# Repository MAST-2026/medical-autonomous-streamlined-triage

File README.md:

# MAST Hackathon Project
Shane Abbott, Justin Amaya, Tyler Marleton, Christian White, Karla "Kenny" Madrigal

## Overview
### Key Design Criteria
Continuous vitals monitoring from wearable patient devices.

Automatic triage status information when patient conditions change.

Real-time transmission of patient data to hospitals.

Reduced workload for EMS personnel, allowing responders to focus on treatment instead of communications.

## Components (Tentative)

### 1. Patient Monitoring Device
Strapped onto the patient as a harness, monitoring vitals such as heart rate, blood pressure, temperature, etc. The deivce would transmit information to the ARU in the vehicle automatically, no human input is necessary.

### 2. Ambulance Repeater Unit
Amplifies transmissions from the patient monitoring device to nearby hospitals. High wattage to counter urban RF environments. Pings the HTU for open beds and/or other qualifying information and services. Receives PMD data.

### 3. Hospital Transciever Unit
Located in the hospital, possibly near the radio equipment. Should have excellent RX capabilities. The final step in the process, this is what the hospital staff see, the end product of all incoming patients, in one place.

_Kenny: Question, could a filtering system allow doctors to subscribe to patient updates in real-time, receiving only information relevant to their assigned cases? Also, how do cases get assigned? I doubt whether any of these questions are within the scope of our project, and I think we're better off focusing on the existing components._

## Project Structure
I'd like for each project inside each directory (electrical/firmware/assembly) to have its own `DECISIONS.md` so we can keep track of... decisions.

I've initialized KiCad and PlatformIO projects in the electrical/firmware directories. Mech team (Christian, Justin, Shane) can decide how they want to structure the assembly directory.

```
├── patient-monitoring-device/
│   ├── electrical
│   ├── firmware
│   ├── assembly
│   └── DECISIONS.md
├── ambulance-repeater/
│   ├── electrical
│   ├── firmware
│   ├── assembly
│   └── DECISIONS.md
├── hospital-transciever/
│   ├── electrical
│   ├── firmware
│   ├── assembly
│   └── DECISIONS.md
│   
└── README.md
```

## Getting Started

### Prerequisites
- PlatformIO is an extension for VSCode. Feel free to check out [this video on YouTube](https://www.youtube.com/watch?v=PYSy_PLjytQ)

## Contributing

1. CLONE the repository, not fork. i mean either way doesnt matter but for the sake of simplicit. yas.
2. Create a feature branch (`git checkout -b feature/your-feature`)
3. Commit changes (`git commit -m 'Add feature'`)
4. Push to branch (`git push origin feature/your-feature`)
5. Open a Pull Request. PRs are to merge from your `feature/` branches to the `main` branch

## TODO

- [ ] Define clear project outcome and success criteria
- [ ] [Add additional tasks]

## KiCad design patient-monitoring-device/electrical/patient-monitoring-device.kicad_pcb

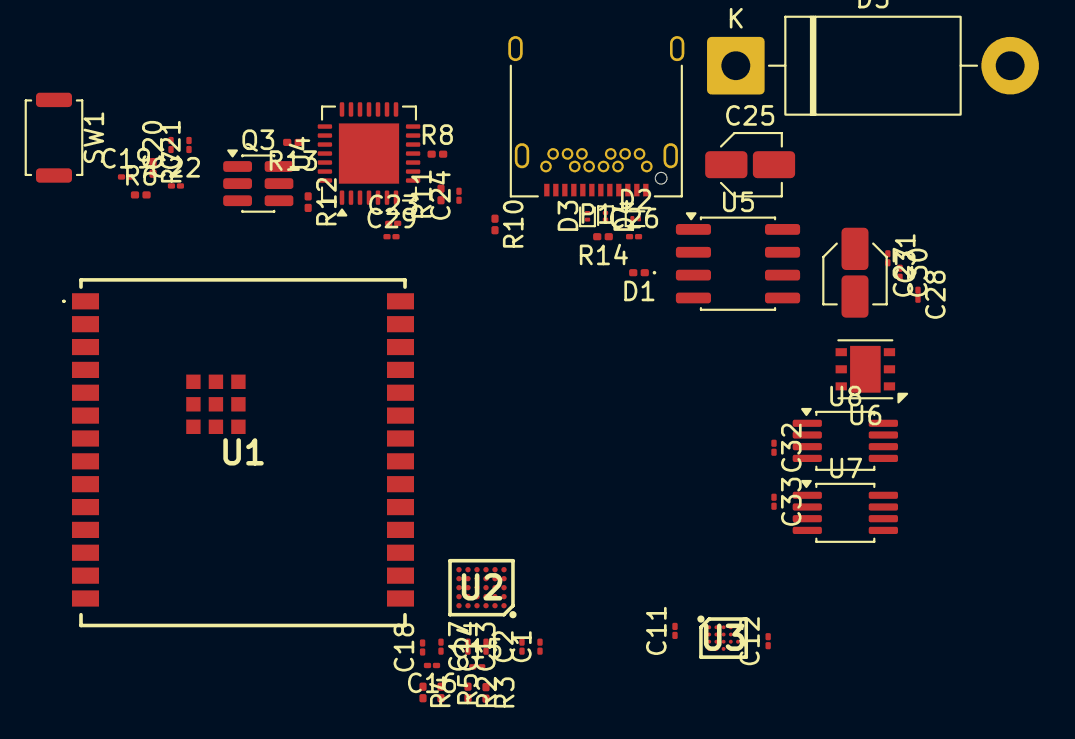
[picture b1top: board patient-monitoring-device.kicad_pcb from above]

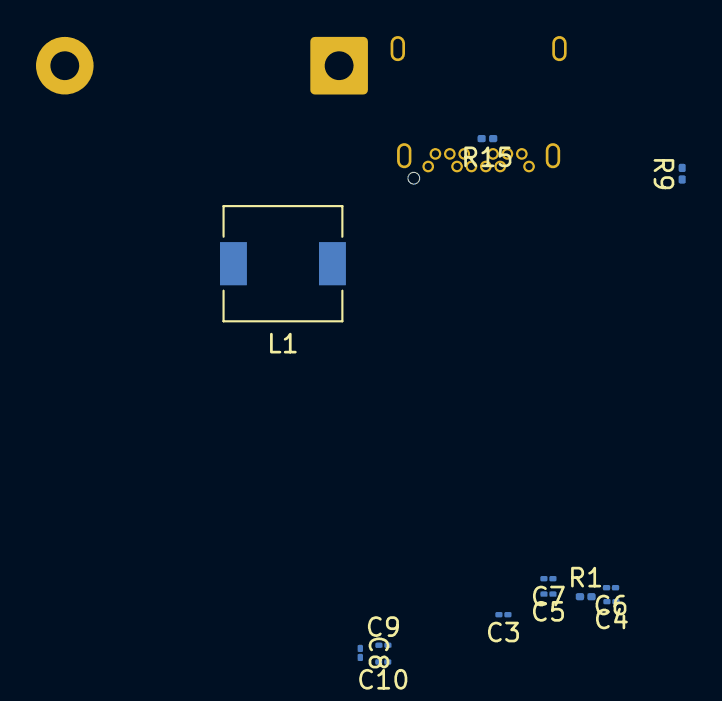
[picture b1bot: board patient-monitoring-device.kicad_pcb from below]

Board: 4 copper layers, 65 parts (12 on the bottom side), 49 nets, no tracks yet.

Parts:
C1, C2: 47n; C_01005_0402Metric
C3, C4, C12, C22: 1u; C_01005_0402Metric
C5, C7, C10, C11, C20, C23: 10u; C_01005_0402Metric
C6: 1n; C_01005_0402Metric
C8, C26: C; C_01005_0402Metric
C9, C19, C21: 0.1u; C_01005_0402Metric
C13, C14, C17, C18: 10p; C_01005_0402Metric
C15: 47p; C_01005_0402Metric
C16: 2n; C_01005_0402Metric
C24: 1u/16V; C_01005_0402Metric
C25, C27: C_Polarized_US; C_Elec_3x5.4
C28, C29, C30, C31, C32, C33: 4.7u; C_01005_0402Metric
D1: D; D_0201_0603Metric
D2, D3, D4: ESD131-B1-W0201; Infineon_SG-WLL-2-3_0.58x0.28_P0.36mm
D5: 1N5820; D_DO-201AD_P15.24mm_Horizontal
L1: L; L_6.3x6.3_H3
P1: USB_C_Plug_USB2.0; USB_C_Receptacle_Amphenol_12401548E4-2A
Q3: MMDTA06; SC-74-6_1.55x2.9mm_P0.95mm
R1: 324k; R_0201_0603Metric
R2, R3: 200; R_0201_0603Metric
R4, R5: 200k; R_0201_0603Metric
R6: 0; R_0201_0603Metric
R7, R12, R13: 10k; R_0201_0603Metric
R8: (NC)10k; R_0201_0603Metric
R9: 1k; R_0201_0603Metric
R10: 22.1k; R_0201_0603Metric
R11: 4.75k; R_0201_0603Metric
R14, R15: 5.1k; R_0201_0603Metric
SW1: push; SW_Push_SPST_NO_Alps_SKRK
U1: ESP32-C6-WROOM-01U; ESP32C6WROOM1UN8
U2: MAX30001
U3: MAX86141
U4: CP2102N-Axx-xQFN28; QFN-28-1EP_5x5mm_P0.5mm_EP3.35x3.35mm
U5: XL1509-5.0; SOIC-8_3.9x4.9mm_P1.27mm
U6: LDO40LPU33RY; DFN-6-1EP_3x3mm_P0.95mm_EP1.7x2.6mm
U7: LT1962-1.8; MSOP-8_3x3mm_P0.65mm
U8: LT1962-2.5; MSOP-8_3x3mm_P0.65mm

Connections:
+1V8: C8.1, C9.1, C33.1, U2.D6 (DVDD), U2.E1 (AVDD), U3.C2 (VDD_{DIG}), U3.D2 (VDD_{ANA}), U7.1 (OUT), U7.2 (SENSE)
+2V5: C32.1, U2.D3 (OVDD), U8.1 (OUT), U8.2 (SENSE)
+3V3: C20.1, C21.1, C23.1, C29.1, R7.1, R9.1, U1.2 (3V3), U4.6 (VDD), U4.7 (VREGIN), U6.4 (Vout), U6.5 (Vsense)
+5V: C11.2, C27.1, C28.1, C30.1, C31.1, D1.1 (K), L1.2, U3.A1 (V_{LED}), U5.3 (FB), U6.2 (EN), U6.3 (Vin), U7.5 (~SHDN), U7.8 (IN), U8.5 (~SHDN), U8.8 (IN)
/ESP/CS_{ECG,R}: U1.11 (IO10), U2.E6 (CSB)
/ESP/CS_{SpO2}: U1.12 (IO11), U3.A5 (CSB)
/ESP/EN: C22.2, Q3.6 (C1), R6.2, R7.2, U1.3 (EN)
/ESP/ESP_{RX}/USB_{TX}: U1.24 (RXD0), U4.26 (TXD)
/ESP/ESP_{TX}/USB_{RX}: U1.25 (TXD0), U4.25 (RXD)
/ESP/FCK: U1.16 (IO18), U2.D5 (FCLK)
/ESP/INT_{B2}: U1.7 (IO7), U2.E2 (INT2B)
/ESP/INT_{B}: U1.6 (IO6), U2.D2 (INTB)
/ESP/INT_{SpO2}: U1.4 (IO4), U3.B2 (INT)
/ESP/IO_{9}: Q3.4 (C2), U1.15 (IO9)
/ESP/MISO: U1.18 (IO20), U2.E3 (SDO), U3.A3 (SDO)
/ESP/MOSI: U1.17 (IO19), U2.E4 (SDI), U3.A4 (SDI)
/ESP/SCK: U1.19 (IO21), U2.E5 (SCLK), U3.A2 (SCLK)
/ESP/usb/USB_{DN}: D3.2 (A2), P1.A7 (D-), P1.B7 (D-), U4.5 (D-)
/ESP/usb/USB_{DP}: D4.2 (A2), P1.A6 (D+), P1.B6 (D+), U4.4 (D+)
/ESP/usbToUART/DTR: Q3.2 (E2), R12.1, U4.28 (~DTR)
/ESP/usbToUART/RTS: Q3.5 (E1), R13.1, U4.24 (~RTS)
/MAX30001/electrode_{N}/Electrode: R3.2, R4.2
/MAX30001/electrode_{P}/Electrode: R2.2, R5.2
GND: C3.2, C5.2, C6.2, C7.2, C8.2, C10.2, C11.1, C12.1, C13.2, C14.1, C17.2, C18.1, C19.1, C20.2, C21.2, C22.1, C23.2, C24.1, C25.2, C26.2, C27.2, C28.2, C29.2, C30.2, C31.2, C32.2, C33.2, D2.2 (A2), D3.1 (A1), D4.1 (A1), D5.2 (A), P1.A1 (GND), P1.A12 (GND), P1.B1 (GND), P1.B12 (GND), P1.S1 (SHIELD), R1.2, R8.2, R11.1, R14.2, R15.2, SW1.1, U1.1 (GND_1), U2.B3 (AGND), U2.B4 (AGND), U2.C3 (AGND), U2.C4 (AGND), U2.C5 (DGND), U2.D4 (AGND), U3.C3 (GND_{DIG}), U3.C4 (GND_{ANA}), U3.D3 (PGND), U4.3 (GND), U4.29 (GND), U5.4 (~EN), U5.5 (GND), U5.6 (GND), U5.7 (GND), U5.8 (GND), U6.1 (GND), U6.7 (GND), U7.4 (GND), U8.4 (GND)
unnamed: C9.2, C10.1
unnamed: C19.2, R6.1, SW1.2
unnamed: D5.1 (K), L1.1, U5.2 (OUT)
unnamed: P1.A5 (CC1), R14.1
unnamed: P1.B5 (CC2), R15.1
unnamed: Q3.1 (B1), R12.2
unnamed: Q3.3 (B2), R13.2
unnamed: C14.2, C15.2, R3.1, U2.A3 (BIN)
unnamed: C13.1, C15.1, R2.1, U2.A4 (BIP)
unnamed: C4.2, U2.B5 (CAPN)
unnamed: C4.1, U2.B6 (CAPP)
unnamed: C6.1, U2.C6 (CPLL)
unnamed: C2.2, U2.A2 (DRVN)
unnamed: C1.2, U2.A1 (DRVP)
unnamed: C16.2, C18.2, R4.1, U2.A6 (ECGN)
unnamed: C16.1, C17.1, R5.1, U2.A5 (ECGP)
unnamed: R1.1, U2.B2 (R_{BIAS})
unnamed: C3.1, U2.B1 (V_{BG})
unnamed: C5.1, U2.C1 (V_{CM})
unnamed: C7.1, U2.D1 (V_{REF})
unnamed: C12.2, U3.B5 (VREF)
unnamed: C24.2, R10.2, R11.2, U4.8 (VBUS)
unnamed: R9.2, U4.9 (~RST)
unnamed: R8.1, U4.11 (~SUSPEND)
V_{BUS}: C25.1, C26.1, D1.2 (A), D2.1 (A1), P1.A4 (VBUS), P1.A9 (VBUS), P1.B4 (VBUS), P1.B9 (VBUS), R10.1, U5.1 (VIN)

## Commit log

2026-03-10 add gitignore
2026-03-10 test
2026-03-11 Revise README components and contribution guidelines
    Updated components section and clarified contributing instructions.
2026-03-12 restructured folders
2026-03-14 pmd: decisions.md: decided on ICs, moving onto schematic
2026-03-14 added max30001 symbool
2026-03-14 a few hours later
